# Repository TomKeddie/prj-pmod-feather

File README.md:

# prj-pmod-feather
Feather plate allow pmod usage

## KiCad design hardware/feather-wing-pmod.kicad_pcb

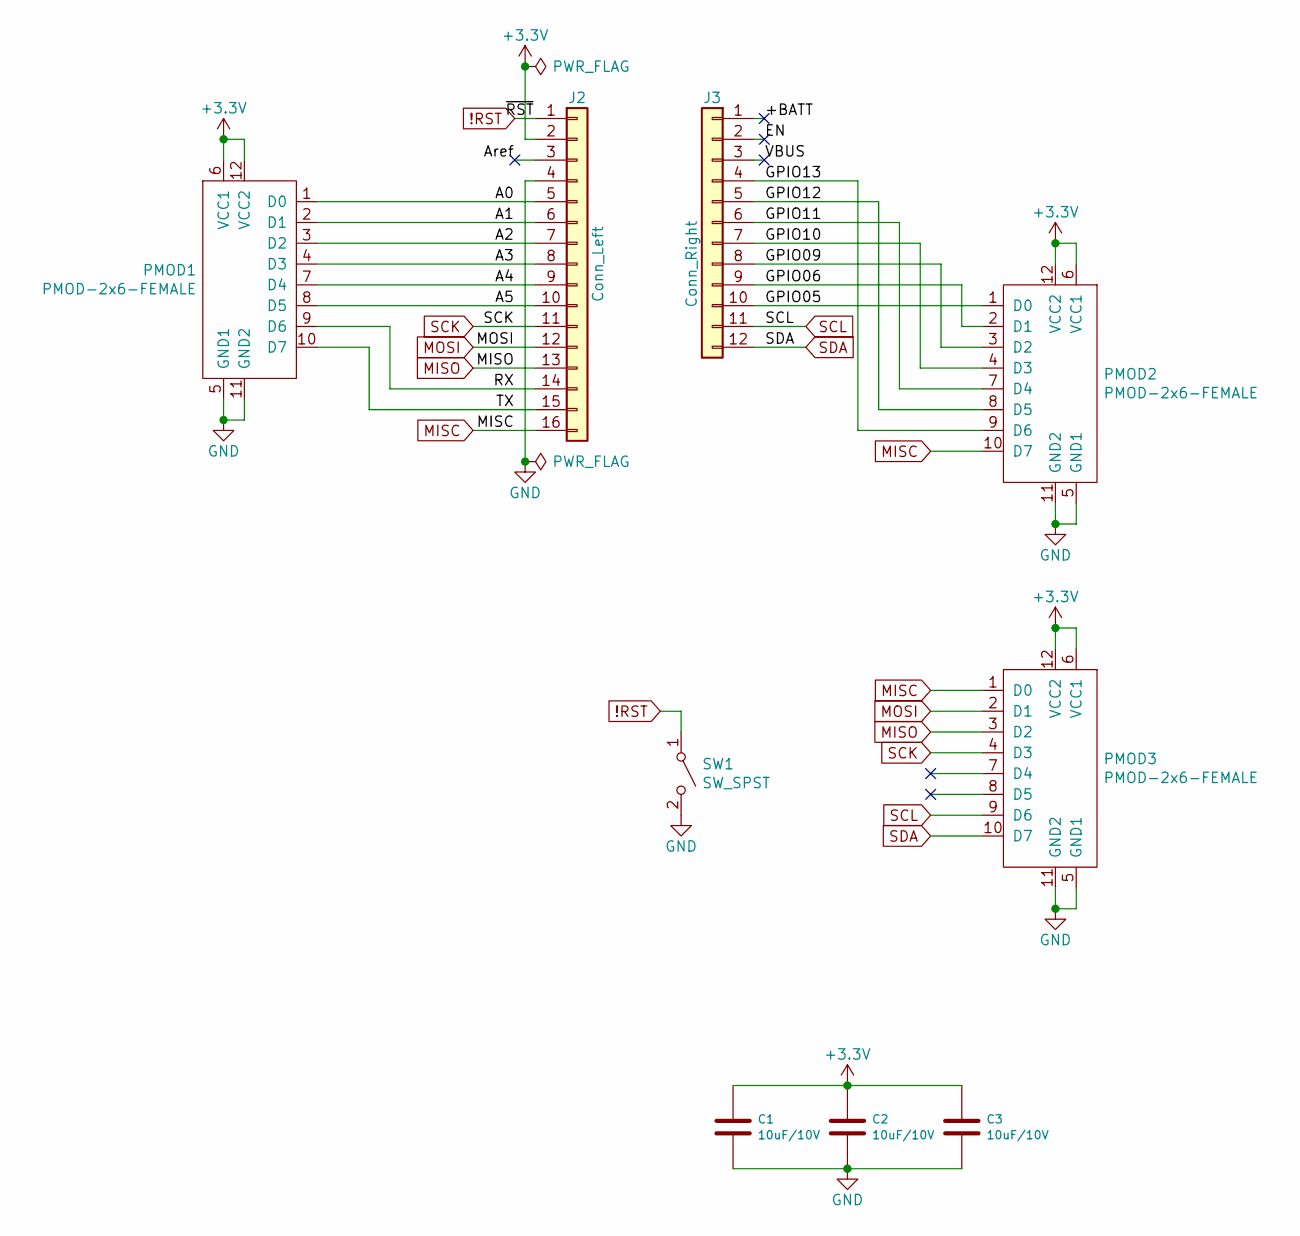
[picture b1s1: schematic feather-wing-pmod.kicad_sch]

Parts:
C1, C2, C3: 10uF/10V; C_0603_1608Metric
J2: Conn_Left; PinSocket_1x16_P2.54mm_Vertical
J3: Conn_Right; PinSocket_1x12_P2.54mm_Vertical
PMOD1, PMOD2: PMOD-2x6-FEMALE; 2X6_SMD_RA_SOCKET
PMOD3: PMOD-2x6-FEMALE; PMOD_2X6_PTH_RA_SOCKET
SW1: SW_SPST; SW_Push_1P1T_NO_CK_KMR2

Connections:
!RST: J2.1, SW1.1 (A)
+3V3: C1.1, C2.1, C3.1, J2.2, PMOD1.6 (VCC1), PMOD1.12 (VCC2), PMOD2.6 (VCC1), PMOD2.12 (VCC2), PMOD3.6 (VCC1), PMOD3.12 (VCC2)
/+BATT: J3.1
/A0: J2.5, PMOD1.1 (D0)
/A1: J2.6, PMOD1.2 (D1)
/A2: J2.7, PMOD1.3 (D2)
/A3: J2.8, PMOD1.4 (D3)
/A4: J2.9, PMOD1.7 (D4)
/A5: J2.10, PMOD1.8 (D5)
/Aref: J2.3
/EN: J3.2
/GPIO05: J3.10, PMOD2.1 (D0)
/GPIO06: J3.9, PMOD2.2 (D1)
/GPIO09: J3.8, PMOD2.3 (D2)
/GPIO10: J3.7, PMOD2.4 (D3)
/GPIO11: J3.6, PMOD2.7 (D4)
/GPIO12: J3.5, PMOD2.8 (D5)
/GPIO13: J3.4, PMOD2.9 (D6)
/RX: J2.14, PMOD1.9 (D6)
/TX: J2.15, PMOD1.10 (D7)
/VBUS: J3.3
GND: C1.2, C2.2, C3.2, J2.4, PMOD1.5 (GND1), PMOD1.11 (GND2), PMOD2.5 (GND1), PMOD2.11 (GND2), PMOD3.5 (GND1), PMOD3.11 (GND2), SW1.2 (B)
MISC: J2.16, PMOD2.10 (D7), PMOD3.1 (D0)
MISO: J2.13, PMOD3.3 (D2)
MOSI: J2.12, PMOD3.2 (D1)
SCK: J2.11, PMOD3.4 (D3)
SCL: J3.11, PMOD3.9 (D6)
SDA: J3.12, PMOD3.10 (D7)

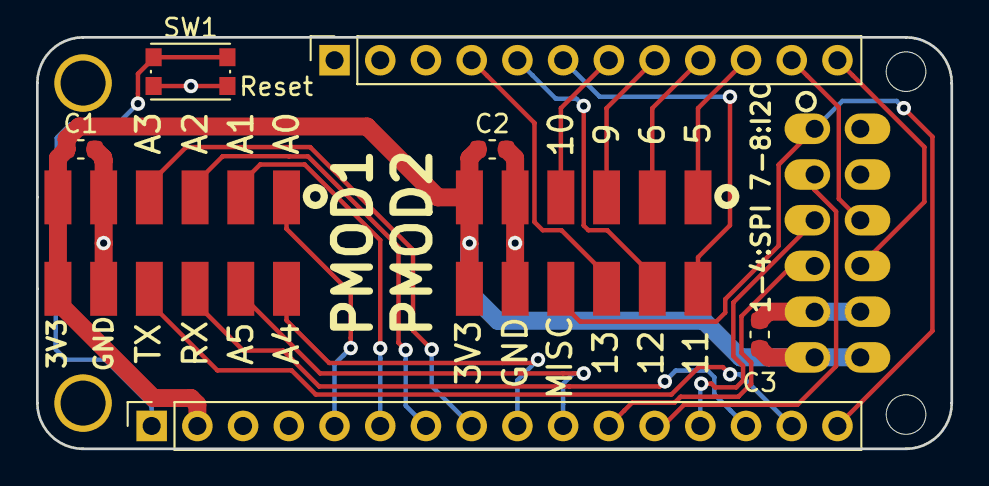
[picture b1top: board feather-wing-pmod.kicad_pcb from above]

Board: 2 copper layers, 50.8 x 22.9 mm, 9 parts (0 on the bottom side), 24 nets.

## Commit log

2019-11-20 v1.0: routed, need silk cleanup
2019-11-21 v1.0: ready for mfg
2019-11-21 v1.0 : add gerber files
2019-11-22 Fix 3d model, add screenshots
2019-11-22 v1.0 as submitted for manufacture
2021-03-27 #1 Upgrade for kicad v6 and add BOM
